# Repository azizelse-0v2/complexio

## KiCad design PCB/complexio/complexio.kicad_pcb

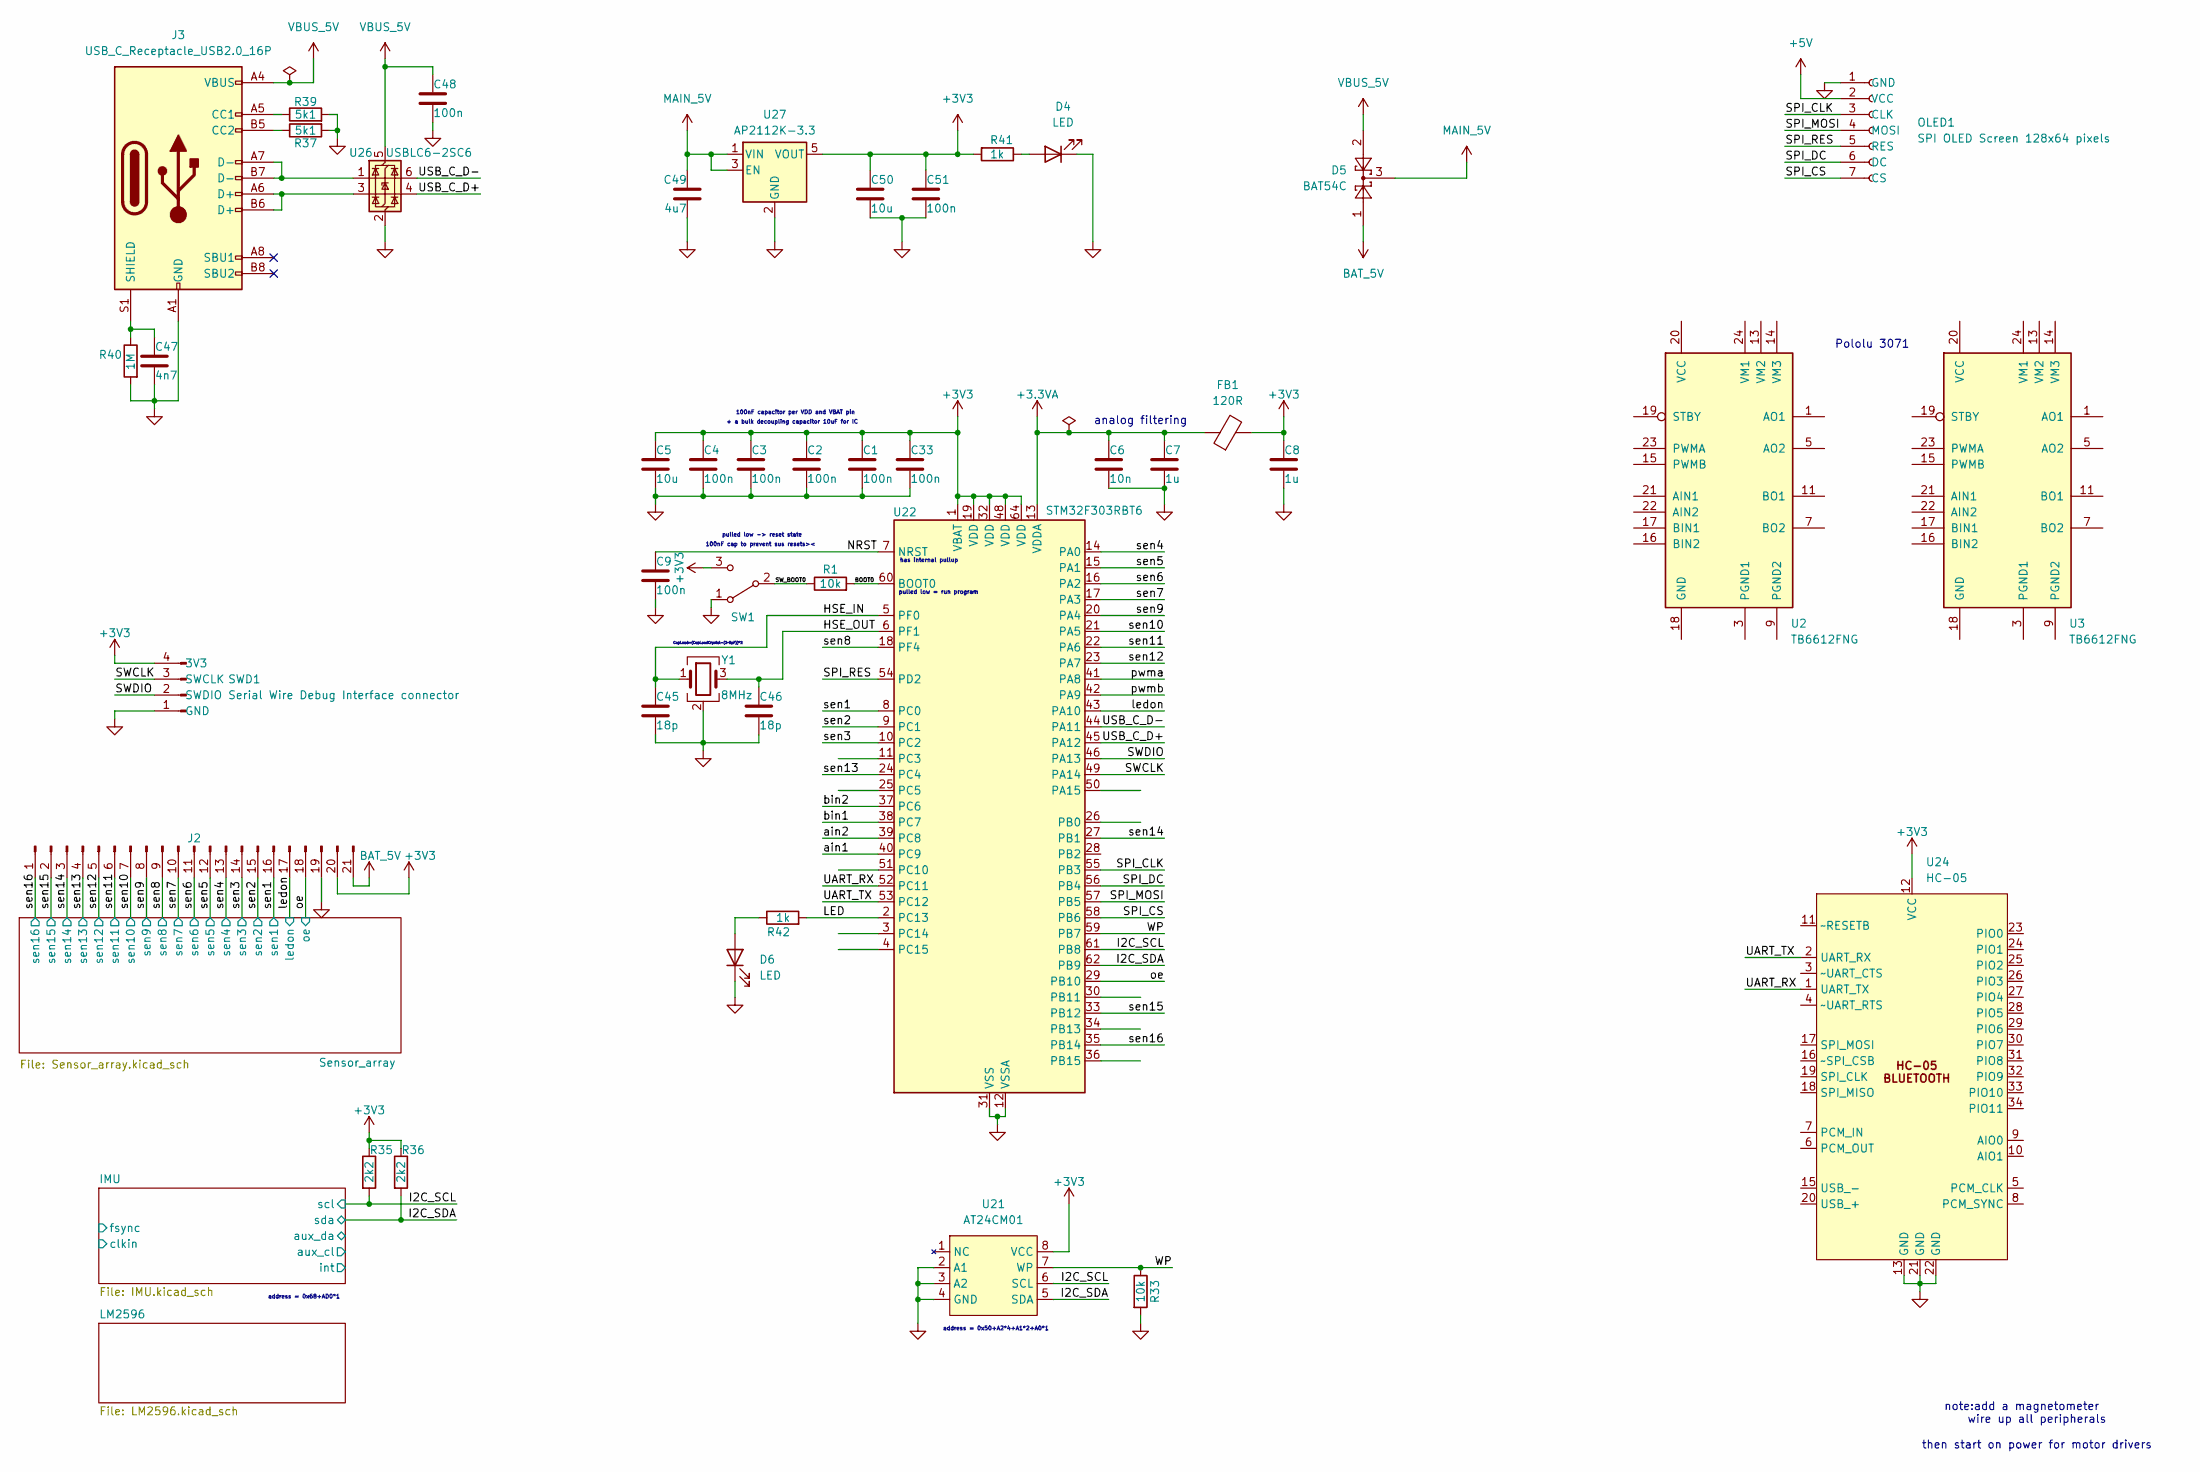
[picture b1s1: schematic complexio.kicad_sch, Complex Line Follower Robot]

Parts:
C1, C2, C3, C4, C9, C33, C48, C51: 100n; C_0402_1005Metric; MFR.Part # CL05B104KO5NNNC; JLCPCB Part # C1525
C5, C50: 10u; C_0603_1608Metric; MFR.Part # CL10A106MQ8NNNC; JLCPCB Part # C1691
C6: 10n; C_0402_1005Metric; MFR.Part # CL05B103KB5NNNC; JLCPCB Part # C15195
C7, C8: 1u; C_0402_1005Metric; MFR.Part # CL05A105KP5NNNC; JLCPCB Part # C14445
C45, C46: 18p; C_0402_1005Metric; MFR.Part # 0402CG180J500NT; JLCPCB Part # C1549
C47: 4n7; C_1206_3216Metric; MFR.Part # 1206B472K501NT; JLCPCB Part # C30323
C49: 4u7; C_0603_1608Metric; MFR.Part # CL10A475KP8NNNC; JLCPCB Part # C1705
D4, D6: LED; LED_0201_0603Metric; MFR.Part # KT-0603R; JLCPCB Part # C2286
D5: BAT54C; SOT-23; MFR.Part # MBR2060CT-LJ; JLCPCB Part # C82585
FB1: 120R; L_0603_1608Metric; MFR.Part # VHF160808H1N8ST; JLCPCB Part # C1026
J2: Conn_01x21_Pin; PinHeader_1x21_P1.27mm_Horizontal; MFR.Part # PZ1.27-1*50; JLCPCB Part # C5360892
J3: USB_C_Receptacle_USB2.0_16P; USB_C_Receptacle_GCT_USB4105-xx-A_16P_TopMnt_Horizontal
OLED1: SPI OLED Screen 128x64 pixels; SSD1306_SPI; MFR.Part # KH-2.54FH-1X7P-H8.5; JLCPCB Part # C2932672
R1, R33: 10k; R_0402_1005Metric; MFR.Part # RCT0210KJLF; JLCPCB Part # C174175
R35, R36: 2k2; R_0603_1608Metric; MFR.Part # 0603WAF2201T5E; JLCPCB Part # C4190
R37, R39: 5k1; R_0603_1608Metric; MFR.Part # 0603WAF5101T5E; JLCPCB Part # C23186
R40: 1M; R_1206_3216Metric; MFR.Part # HR1206J1M00P05Z; JLCPCB Part # C175518
R41, R42: 1k; R_1206_3216Metric; MFR.Part # 1206W4J0102T5E; JLCPCB Part # C1469
SW1: SW_SPDT; SW_E-Switch_EG1224_SPDT_Angled; MFR.Part # EG1224; JLCPCB Part # C273395
SWD1: Serial Wire Debug Interface connector; PinHeader_1x04_P2.54mm_Horizontal; MFR.Part # 2.54-1*4P反弯排针; JLCPCB Part # C91552
U2, U3: TB6612FNG; SSOP-24_5.3x8.2mm_P0.65mm; MFR.Part # TB6612FNG,C,8,EL; JLCPCB Part # C141517
U21: AT24CM01; MFR.Part # AT24CM01-SHD-T; JLCPCB Part # C36057
U22: STM32F303RBT6; LQFP-64_10x10mm_P0.5mm; MFR.Part # STM32F303RBT6; JLCPCB Part # C130453
U24: HC-05; HC-05_SMD
U26: USBLC6-2SC6; SOT-23-6
U27: AP2112K-3.3; SOT-23-5
Y1: 8MHz; Crystal_SMD_3225-4Pin_3.2x2.5mm; MFR.Part # XXDCELNANF-8MHZ

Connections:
+3.3VA: C6.1, C7.1, FB1.1, U22.13 (VDDA)
+3V3: C1.1, C2.1, C3.1, C4.1, C5.1, C8.1, C33.1, C50.1, C51.1, FB1.2, J2.20, R35.1, R36.1, R41.2, SW1.3 (C), SWD1.4 (3V3), U21.8 (VCC), U22.1 (VBAT), U22.19 (VDD), U22.32 (VDD), U22.48 (VDD), U22.64 (VDD), U24.12 (VCC), U27.5 (VOUT); also elsewhere on the board
+5V: OLED1.2 (VCC)
/BOOT0: R1.2, U22.60 (BOOT0)
/HSE_IN: C45.1, U22.5 (PF0), Y1.1
/HSE_OUT: C46.1, U22.6 (PF1), Y1.3
/I2C_SCL: R35.2, U21.6 (SCL), U22.61 (PB8); also elsewhere on the board
/I2C_SDA: R36.2, U21.5 (SDA), U22.62 (PB9); also elsewhere on the board
/LED: R42.2, U22.2 (PC13)
/NRST: C9.1, U22.7 (NRST)
/SPI_CLK: OLED1.3 (CLK), U22.55 (PB3)
/SPI_CS: OLED1.7 (CS), U22.58 (PB6)
/SPI_DC: OLED1.6 (DC), U22.56 (PB4)
/SPI_MOSI: OLED1.4 (MOSI), U22.57 (PB5)
/SPI_RES: OLED1.5 (RES), U22.54 (PD2)
/SWCLK: SWD1.3 (SWCLK), U22.49 (PA14)
/SWDIO: SWD1.2 (SWDIO), U22.46 (PA13)
/SW_BOOT0: R1.1, SW1.2 (B)
/UART_RX: U22.52 (PC11), U24.1 (UART_TX)
/UART_TX: U22.53 (PC12), U24.2 (UART_RX)
/USB_C_D+: U22.45 (PA12), U26.4 (I/O2)
/USB_C_D-: U22.44 (PA11), U26.6 (I/O1)
/WP: R33.1, U21.7 (WP), U22.59 (PB7)
/ain1: U22.40 (PC9)
/ain2: U22.39 (PC8)
/bin1: U22.38 (PC7)
/bin2: U22.37 (PC6)
/ledon: J2.17, U22.43 (PA10); also elsewhere on the board
/oe: J2.18, U22.29 (PB10); also elsewhere on the board
/pwma: U22.41 (PA8)
/pwmb: U22.42 (PA9)
/sen1: J2.16, U22.8 (PC0); also elsewhere on the board
/sen2: J2.15, U22.9 (PC1); also elsewhere on the board
/sen3: J2.14, U22.10 (PC2); also elsewhere on the board
/sen4: J2.13, U22.14 (PA0); also elsewhere on the board
/sen5: J2.12, U22.15 (PA1); also elsewhere on the board
/sen6: J2.11, U22.16 (PA2); also elsewhere on the board
/sen7: J2.10, U22.17 (PA3); also elsewhere on the board
/sen8: J2.9, U22.18 (PF4); also elsewhere on the board
/sen9: J2.8, U22.20 (PA4); also elsewhere on the board
/sen10: J2.7, U22.21 (PA5); also elsewhere on the board
/sen11: J2.6, U22.22 (PA6); also elsewhere on the board
/sen12: J2.5, U22.23 (PA7); also elsewhere on the board
/sen13: J2.4, U22.24 (PC4); also elsewhere on the board
/sen14: J2.3, U22.27 (PB1); also elsewhere on the board
/sen15: J2.2, U22.33 (PB12); also elsewhere on the board
/sen16: J2.1, U22.35 (PB14); also elsewhere on the board
BAT_5V: D5.1, J2.21; also elsewhere on the board
GND: C1.2, C2.2, C3.2, C4.2, C5.2, C6.2, C7.2, C8.2, C9.2, C33.2, C45.2, C46.2, C47.2, C48.2, C49.2, C50.2, C51.2, D4.1 (K), D6.1 (K), J2.19, J3.A1 (GND), J3.A12 (GND), J3.B1 (GND), J3.B12 (GND), OLED1.1 (GND), R33.2, R37.2, R39.2, R40.2, SW1.1 (A), SWD1.1 (GND), U21.2 (A1), U21.3 (A2), U21.4 (GND), U22.12 (VSSA), U22.31 (VSS), U22.47 (VSS), U22.63 (VSS), U24.13 (GND), U24.21 (GND), U24.22 (GND), U26.2 (GND), U27.2 (GND), Y1.2 (G), Y1.4 (G); also elsewhere on the board
MAIN_5V: C49.1, D5.3, U27.1 (VIN), U27.3 (EN); also elsewhere on the board
unnamed: D4.2 (A), R41.1
unnamed: D6.2 (A), R42.1
unnamed: J3.A5 (CC1), R39.1
unnamed: J3.B5 (CC2), R37.1
unnamed: J3.A6 (D+), J3.B6 (D+), U26.3 (I/O2)
unnamed: J3.A7 (D-), J3.B7 (D-), U26.1 (I/O1)
unnamed: C47.1, J3.S1 (SHIELD), R40.1
unnamed: U2.1 (AO1), U2.2 (AO1)
unnamed: U2.5 (AO2), U2.6 (AO2)
unnamed: U2.11 (BO1), U2.12 (BO1)
unnamed: U2.7 (BO2), U2.8 (BO2)
unnamed: U2.3 (PGND1), U2.4 (PGND1)
unnamed: U2.9 (PGND2), U2.10 (PGND2)
unnamed: U3.1 (AO1), U3.2 (AO1)
unnamed: U3.5 (AO2), U3.6 (AO2)
unnamed: U3.11 (BO1), U3.12 (BO1)
unnamed: U3.7 (BO2), U3.8 (BO2)
unnamed: U3.3 (PGND1), U3.4 (PGND1)
unnamed: U3.9 (PGND2), U3.10 (PGND2)
VBUS_5V: C48.1, D5.2, J3.A4 (VBUS), J3.A9 (VBUS), J3.B4 (VBUS), J3.B9 (VBUS), U26.5 (VBUS)

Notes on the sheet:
+ a bulk decoupling capacitor 10uF for IC
pulled low -> reset state
100nF capacitor per VDD and VBAT pin
has internal pullup
note:add a magnetometer wire up all peripherals then start on power for motor drivers
address = 0x68+AD0*1
analog filtering
100nF cap to prevent sus resets><
pulled low = run program
Pololu 3071
address = 0x50+A2*4+A1*2+A0*1
CapLoad=(CapLoadCrystal-(3~5pF))*2

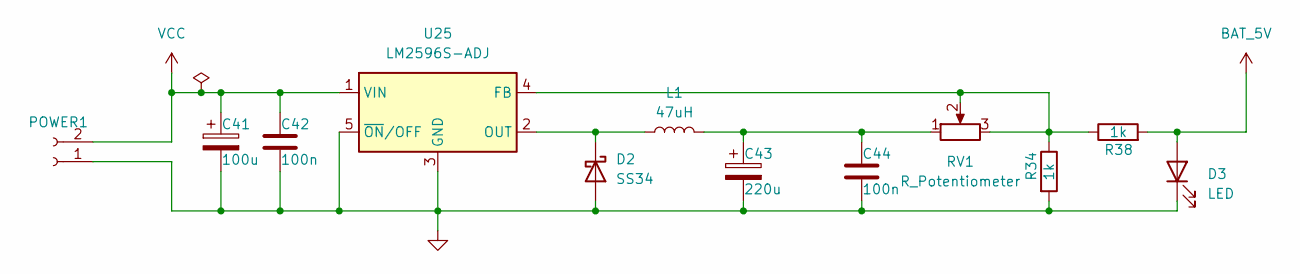
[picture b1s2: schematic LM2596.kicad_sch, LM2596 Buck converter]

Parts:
C41: 100u; CP_Elec_8x10
C42, C44: 100n; C_0402_1005Metric; MFR.Part # CL05B104KO5NNNC; JLCPCB Part # C1525
C43: 220u; CP_Elec_8x10
D2: SS34; D_SMA; MFR.Part # B340LA-13-F; JLCPCB Part # C17101
D3: LED; LED_0201_0603Metric; MFR.Part # KT-0603R; JLCPCB Part # C2286
L1: 47uH; L_Bourns_SRR1208_12.7x12.7mm
POWER1: Conn_01x02_Socket; AMASS_XT60-M_1x02_P7.20mm_Vertical; MFR.Part # XT60-M.; JLCPCB Part # C98733
R34, R38: 1k; R_1206_3216Metric; MFR.Part # 1206W4J0102T5E; JLCPCB Part # C1469
RV1: R_Potentiometer; Potentiometer_Bourns_3296W_Vertical
U25: LM2596S-ADJ; TO-263-5_TabPin3; MFR.Part # LM2596R-ADJ; JLCPCB Part # C52684

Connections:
BAT_5V: D3.2 (A), R38.2; also elsewhere on the board
GND: C41.2, C42.2, C43.2, C44.2, D2.2 (A), D3.1 (K), POWER1.1, R34.2, U25.3 (GND), U25.5 (~ON/OFF); also elsewhere on the board
unnamed: C43.1, C44.1, L1.2, RV1.1
unnamed: D2.1 (K), L1.1, U25.2 (OUT)
unnamed: R34.1, R38.1, RV1.2, RV1.3, U25.4 (FB)
VCC: C41.1, C42.1, POWER1.2, U25.1 (VIN)

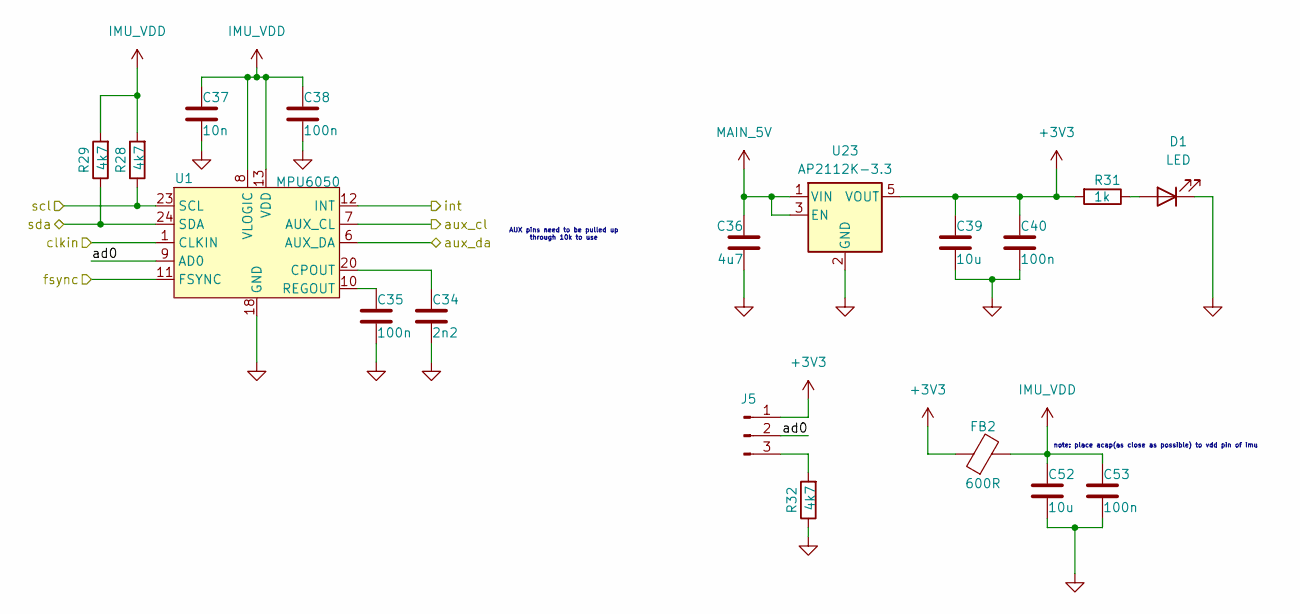
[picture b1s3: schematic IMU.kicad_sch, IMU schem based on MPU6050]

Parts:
C34: 2n2; C_0402_1005Metric; MFR.Part # CC0402KRX7R9BB222; JLCPCB Part # C106861
C35, C38, C40, C53: 100n; C_0402_1005Metric; MFR.Part # CL05B104KO5NNNC; JLCPCB Part # C1525
C36: 4u7; C_0603_1608Metric; MFR.Part # CL10A475KP8NNNC; JLCPCB Part # C1705
C37: 10n; C_0402_1005Metric; MFR.Part # CL05B103KB5NNNC; JLCPCB Part # C15195
C39, C52: 10u; C_0603_1608Metric; MFR.Part # CL10A106MQ8NNNC; JLCPCB Part # C1691
D1: LED; LED_0201_0603Metric; MFR.Part # KT-0603R; JLCPCB Part # C2286
FB2: 600R; L_0603_1608Metric; MFR.Part # BLM18AG601SN1D; JLCPCB Part # C19330
J5: Conn_01x03_Pin; PinSocket_1x03_P2.54mm_Vertical; MFR.Part # 2.54-1*3PPin; JLCPCB Part # C49257
R28, R29, R32: 4k7; R_0402_1005Metric; MFR.Part # 0402WGF4701TCE; JLCPCB Part # C25900
R31: 1k; R_1206_3216Metric; MFR.Part # 1206W4J0102T5E; JLCPCB Part # C1469
U1: MPU6050; MPU6050SMD
U23: AP2112K-3.3; SOT-23-5

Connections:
+3V3: C39.1, C40.1, FB2.1, J5.1, R31.2, U23.5 (VOUT); also elsewhere on the board
/I2C_SCL: R28.1, U1.23 (SCL); also elsewhere on the board
/I2C_SDA: R29.1, U1.24 (SDA); also elsewhere on the board
/IMU/ad0: J5.2, U1.9 (AD0)
/IMU/aux_cl: U1.7 (AUX_CL)
/IMU/aux_da: U1.6 (AUX_DA)
/IMU/clkin: U1.1 (CLKIN)
/IMU/fsync: U1.11 (FSYNC)
/IMU/int: U1.12 (INT)
GND: C34.2, C35.2, C36.2, C37.2, C38.2, C39.2, C40.2, C52.2, C53.2, D1.1 (K), R32.1, U1.18 (GND), U23.2 (GND); also elsewhere on the board
IMU_VDD: C37.1, C38.1, C52.1, C53.1, FB2.2, R28.2, R29.2, U1.8 (VLOGIC), U1.13 (VDD)
MAIN_5V: C36.1, U23.1 (VIN), U23.3 (EN); also elsewhere on the board
unnamed: D1.2 (A), R31.1
unnamed: J5.3, R32.2
unnamed: C34.1, U1.20 (CPOUT)
unnamed: C35.1, U1.10 (REGOUT)

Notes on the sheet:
AUX pins need to be pulled up through 10k to use
note: place acap(as close as possible) to vdd pin of imu

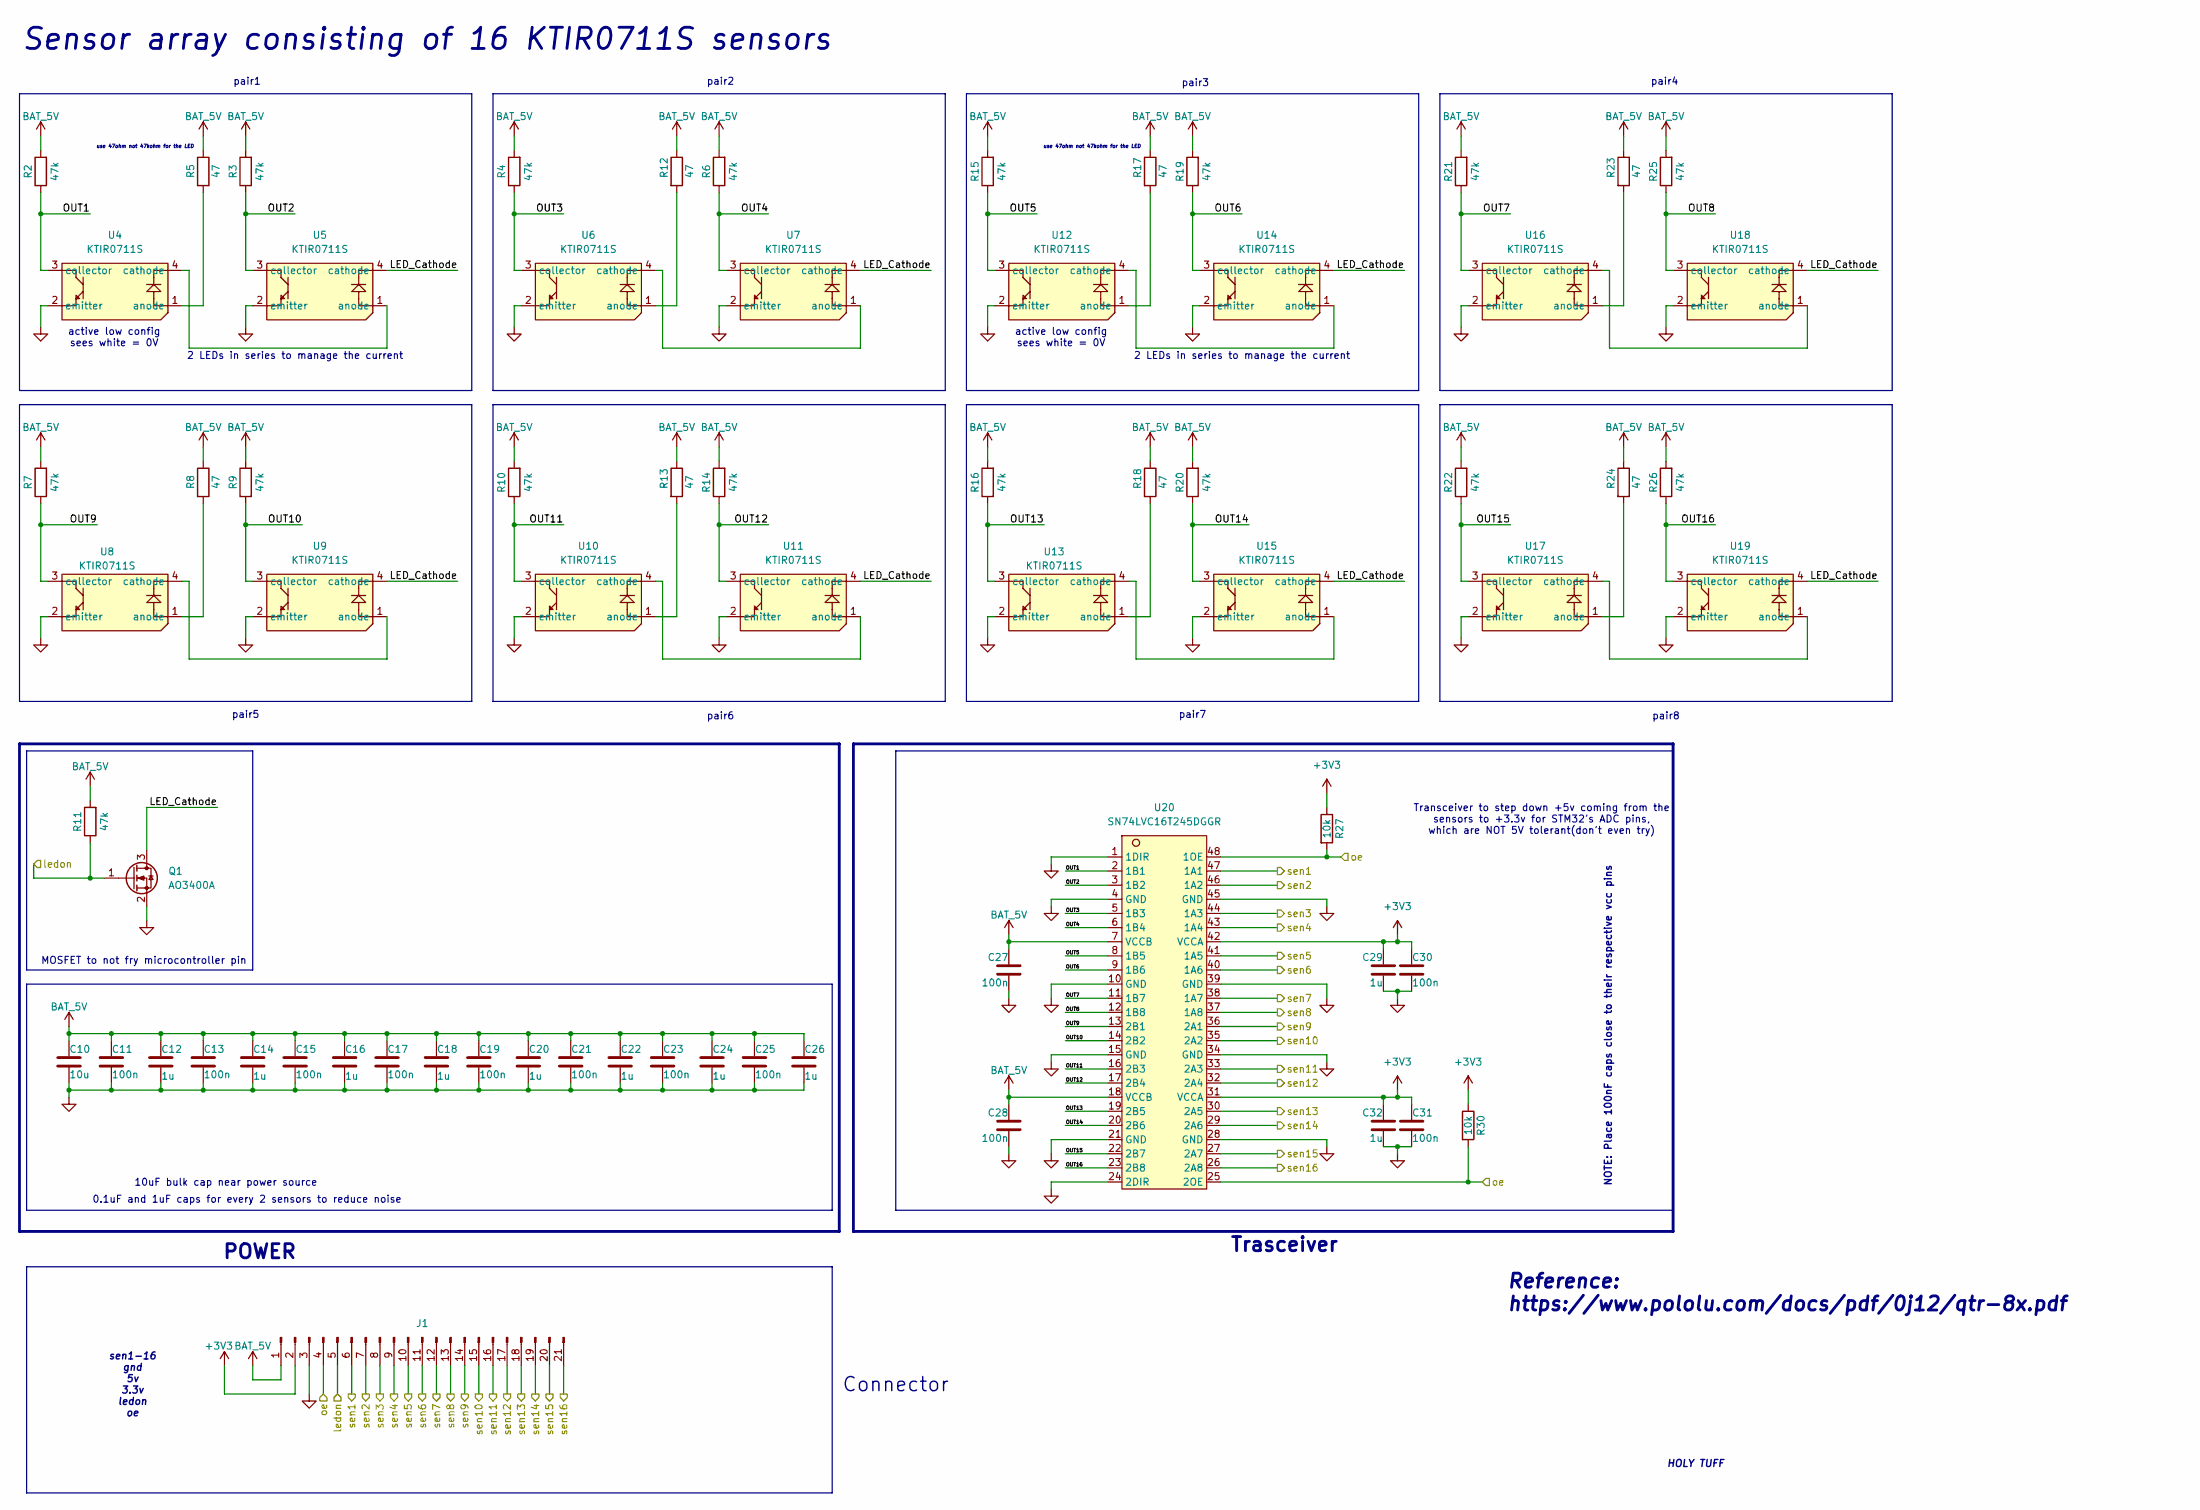
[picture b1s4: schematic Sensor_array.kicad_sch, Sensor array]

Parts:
C10: 10u; C_0603_1608Metric; MFR.Part # CL10A106MQ8NNNC; JLCPCB Part # C1691
C11, C13, C15, C17, C19, C21, C23, C25, C27, C28, C30, C31: 100n; C_0402_1005Metric; MFR.Part # CL05B104KO5NNNC; JLCPCB Part # C1525
C12, C14, C16, C18, C20, C22, C24, C26, C29, C32: 1u; C_0402_1005Metric; MFR.Part # CL05A105KP5NNNC; JLCPCB Part # C14445
J1: Conn_01x21_Pin; PinHeader_1x21_P1.27mm_Horizontal; MFR.Part # PZ1.27-1*50; JLCPCB Part # C5360892
Q1: AO3400A; SOT-23
R2, R3, R4, R6, R7, R9, R10, R11, R14, R15, R16, R19, R20, R21, R22, R25, R26: 47k; R_0402_1005Metric; MFR.Part # RCA0247KJLF; JLCPCB Part # C22356233
R5, R8, R12, R13, R17, R18, R23, R24: 47; R_1206_3216Metric; MFR.Part # RCT0647RJLF; JLCPCB Part # C702856
R27, R30: 10k; R_0402_1005Metric; MFR.Part # RCT0210KJLF; JLCPCB Part # C174175
U4, U5, U6, U7, U8, U9, U10, U11, U12, U13, U14, U15, U16, U17, U18, U19: KTIR0711S; MFR.Part # KTIR0711S; JLCPCB Part # C3034700
U20: SN74LVC16T245DGGR

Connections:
+3V3: C29.1, C30.1, C31.1, C32.1, J1.2, R27.1, R30.1, U20.31 (VCCA), U20.42 (VCCA); also elsewhere on the board
/Sensor_array/LED_Cathode: Q1.3 (D), U5.4 (cathode), U7.4 (cathode), U9.4 (cathode), U11.4 (cathode), U14.4 (cathode), U15.4 (cathode), U18.4 (cathode), U19.4 (cathode)
/Sensor_array/OUT1: R2.1, U4.3 (collector), U20.2 (1B1)
/Sensor_array/OUT2: R3.1, U5.3 (collector), U20.3 (1B2)
/Sensor_array/OUT3: R4.1, U6.3 (collector), U20.5 (1B3)
/Sensor_array/OUT4: R6.1, U7.3 (collector), U20.6 (1B4)
/Sensor_array/OUT5: R15.1, U12.3 (collector), U20.8 (1B5)
/Sensor_array/OUT6: R19.1, U14.3 (collector), U20.9 (1B6)
/Sensor_array/OUT7: R21.1, U16.3 (collector), U20.11 (1B7)
/Sensor_array/OUT8: R25.1, U18.3 (collector), U20.12 (1B8)
/Sensor_array/OUT9: R7.1, U8.3 (collector), U20.13 (2B1)
/Sensor_array/OUT10: R9.1, U9.3 (collector), U20.14 (2B2)
/Sensor_array/OUT11: R10.1, U10.3 (collector), U20.16 (2B3)
/Sensor_array/OUT12: R14.1, U11.3 (collector), U20.17 (2B4)
/Sensor_array/OUT13: R16.1, U13.3 (collector), U20.19 (2B5)
/Sensor_array/OUT14: R20.1, U15.3 (collector), U20.20 (2B6)
/Sensor_array/OUT15: R22.1, U17.3 (collector), U20.22 (2B7)
/Sensor_array/OUT16: R26.1, U19.3 (collector), U20.23 (2B8)
/ledon: J1.5, Q1.1 (G), R11.1; also elsewhere on the board
/oe: J1.4, R27.2, R30.2, U20.25 (2OE), U20.48 (1OE); also elsewhere on the board
/sen1: J1.6, U20.47 (1A1); also elsewhere on the board
/sen2: J1.7, U20.46 (1A2); also elsewhere on the board
/sen3: J1.8, U20.44 (1A3); also elsewhere on the board
/sen4: J1.9, U20.43 (1A4); also elsewhere on the board
/sen5: J1.10, U20.41 (1A5); also elsewhere on the board
/sen6: J1.11, U20.40 (1A6); also elsewhere on the board
/sen7: J1.12, U20.38 (1A7); also elsewhere on the board
/sen8: J1.13, U20.37 (1A8); also elsewhere on the board
/sen9: J1.14, U20.36 (2A1); also elsewhere on the board
/sen10: J1.15, U20.35 (2A2); also elsewhere on the board
/sen11: J1.16, U20.33 (2A3); also elsewhere on the board
/sen12: J1.17, U20.32 (2A4); also elsewhere on the board
/sen13: J1.18, U20.30 (2A5); also elsewhere on the board
/sen14: J1.19, U20.29 (2A6); also elsewhere on the board
/sen15: J1.20, U20.27 (2A7); also elsewhere on the board
/sen16: J1.21, U20.26 (2A8); also elsewhere on the board
BAT_5V: C10.1, C11.1, C12.1, C13.1, C14.1, C15.1, C16.1, C17.1, C18.1, C19.1, C20.1, C21.1, C22.1, C23.1, C24.1, C25.1, C26.1, C27.1, C28.1, J1.1, R2.2, R3.2, R4.2, R5.1, R6.2, R7.2, R8.1, R9.2, R10.2, R11.2, R12.1, R13.1, R14.2, R15.2, R16.2, R17.1, R18.1, R19.2, R20.2, R21.2, R22.2, R23.1, R24.1, R25.2, R26.2, U20.7 (VCCB), U20.18 (VCCB); also elsewhere on the board
GND: C10.2, C11.2, C12.2, C13.2, C14.2, C15.2, C16.2, C17.2, C18.2, C19.2, C20.2, C21.2, C22.2, C23.2, C24.2, C25.2, C26.2, C27.2, C28.2, C29.2, C30.2, C31.2, C32.2, J1.3, Q1.2 (S), U4.2 (emitter), U5.2 (emitter), U6.2 (emitter), U7.2 (emitter), U8.2 (emitter), U9.2 (emitter), U10.2 (emitter), U11.2 (emitter), U12.2 (emitter), U13.2 (emitter), U14.2 (emitter), U15.2 (emitter), U16.2 (emitter), U17.2 (emitter), U18.2 (emitter), U19.2 (emitter), U20.1 (1DIR), U20.4 (GND), U20.10 (GND), U20.15 (GND), U20.21 (GND), U20.24 (2DIR), U20.28 (GND), U20.34 (GND), U20.39 (GND), U20.45 (GND); also elsewhere on the board
unnamed: R5.2, U4.1 (anode)
unnamed: U4.4 (cathode), U5.1 (anode)
unnamed: R12.2, U6.1 (anode)
unnamed: U6.4 (cathode), U7.1 (anode)
unnamed: R8.2, U8.1 (anode)
unnamed: U8.4 (cathode), U9.1 (anode)
unnamed: R13.2, U10.1 (anode)
unnamed: U10.4 (cathode), U11.1 (anode)
unnamed: R17.2, U12.1 (anode)
unnamed: U12.4 (cathode), U14.1 (anode)
unnamed: R18.2, U13.1 (anode)
unnamed: U13.4 (cathode), U15.1 (anode)
unnamed: R23.2, U16.1 (anode)
unnamed: U16.4 (cathode), U18.1 (anode)
unnamed: R24.2, U17.1 (anode)
unnamed: U17.4 (cathode), U19.1 (anode)

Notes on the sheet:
2 LEDs in series to manage the current
Reference: https://www.pololu.com/docs/pdf/0j12/qtr-8x.pdf
pair8
sen1-16 gnd 5v 3.3v ledon oe
0.1uF and 1uF caps for every 2 sensors to reduce noise
Trasceiver
pair2
pair5
pair3
NOTE: Place 100nF caps close to their respective vcc pins
Sensor array consisting of 16 KTIR0711S sensors
HOLY TUFF
pair4
pair1
MOSFET to not fry microcontroller pin
pair7
POWER
Connector
pair6
active low config sees white = 0V
10uF bulk cap near power source
use 47ohm not 47kohm for the LED
Transceiver to step down +5v coming from the sensors to +3.3v for STM32's ADC pins, which are NOT 5V tolerant(don't even try)

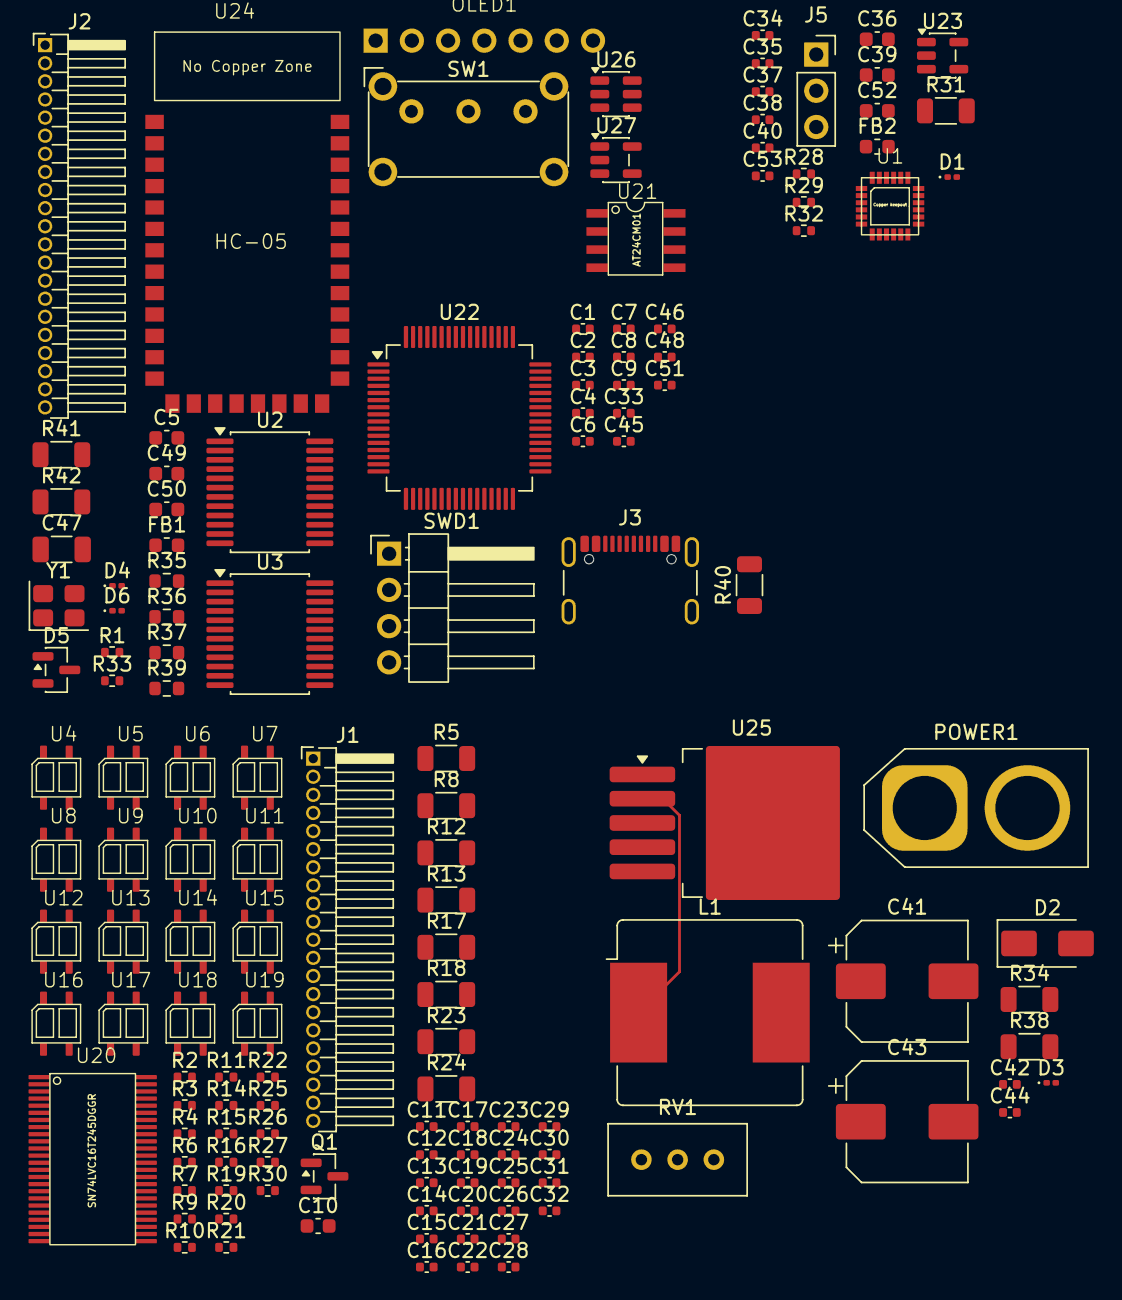
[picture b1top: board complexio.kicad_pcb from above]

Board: 2 copper layers, 142 parts (0 on the bottom side), 106 nets.

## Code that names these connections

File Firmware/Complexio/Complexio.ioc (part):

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Mcu.Name=STM32F303R(B-C)Tx
Mcu.Package=LQFP64
Mcu.UserName=STM32F303RBTx
PA0.GPIOParameters=GPIO_Label
PA0.GPIO_Label=sen4
PA0.Mode=IN1-Single-Ended
PA0.Signal=ADC1_IN1
PA1.GPIOParameters=GPIO_Label
PA1.GPIO_Label=sen5
PA1.Mode=IN2-Single-Ended
PA1.Signal=ADC1_IN2
PA11.Mode=Device
PA11.Signal=USB_DM
PA12.Mode=Device
PA12.Signal=USB_DP
PA13.Mode=Serial_Wire
PA13.Signal=SYS_JTMS-SWDIO
PA14.Mode=Serial_Wire
PA14.Signal=SYS_JTCK-SWCLK
PA2.GPIOParameters=GPIO_Label
PA2.GPIO_Label=sen6
PA2.Mode=IN3-Single-Ended
PA2.Signal=ADC1_IN3
PA3.GPIOParameters=GPIO_Label
PA3.GPIO_Label=sen7
PA3.Mode=IN4-Single-Ended
PA3.Signal=ADC1_IN4
PA4.GPIOParameters=GPIO_Label
PA4.GPIO_Label=sen9
PA4.Mode=IN1-Single-Ended
PA4.Signal=ADC2_IN1
PA5.GPIOParameters=GPIO_Label
PA5.GPIO_Label=sen10
PA5.Mode=IN2-Single-Ended
PA5.Signal=ADC2_IN2
PA6.GPIOParameters=GPIO_Label
PA6.GPIO_Label=sen11
PA6.Mode=IN3-Single-Ended
PA6.Signal=ADC2_IN3
PA7.GPIOParameters=GPIO_Label
PA7.GPIO_Label=sen12
PA7.Mode=IN4-Single-Ended
PA7.Signal=ADC2_IN4
PA8.GPIOParameters=GPIO_Label
PA8.GPIO_Label=pwma
PA8.Signal=S_TIM1_CH1
PA9.GPIOParameters=GPIO_Label
PA9.GPIO_Label=pwmb
PA9.Signal=S_TIM1_CH2
PB1.GPIOParameters=GPIO_Label
PB1.GPIO_Label=sen14
PB1.Mode=IN1-Single-Ended
PB1.Signal=ADC3_IN1
PB12.GPIOParameters=GPIO_Label
PB12.GPIO_Label=sen15
PB12.Mode=IN3-Single-Ended
PB12.Signal=ADC4_IN3
PB14.GPIOParameters=GPIO_Label
PB14.GPIO_Label=sen16
PB14.Mode=IN4-Single-Ended
PB14.Signal=ADC4_IN4
PB3.Mode=Simplex_Bidirectional_Master
PB3.Signal=SPI1_SCK
PB4.GPIOParameters=GPIO_Label
PB4.GPIO_Label=DC
PB4.Signal=GPIO_Output
PB5.Mode=Simplex_Bidirectional_Master
PB5.Signal=SPI1_MOSI
PB6.GPIOParameters=GPIO_Label
PB6.GPIO_Label=CS
PB6.Signal=GPIO_Output
PB8.Mode=I2C
PB8.Signal=I2C1_SCL
PB9.Mode=I2C
PB9.Signal=I2C1_SDA
PC0.GPIOParameters=GPIO_Label
PC0.GPIO_Label=sen1
PC0.Signal=ADCx_IN6
PC1.GPIOParameters=GPIO_Label
PC1.GPIO_Label=sen2
PC1.Signal=ADCx_IN7
PC10.GPIOParameters=GPIO_Label
PC10.GPIO_Label=tx
PC10.Mode=Asynchronous
PC10.Signal=UART4_TX
PC11.GPIOParameters=GPIO_Label
PC11.GPIO_Label=rx
PC11.Mode=Asynchronous
PC11.Signal=UART4_RX
PC13.GPIOParameters=GPIO_Label
PC13.GPIO_Label=LED
PC13.Signal=GPIO_Output
PC2.GPIOParameters=GPIO_Label
PC2.GPIO_Label=sen3
PC2.Signal=ADCx_IN8
PC4.GPIOParameters=GPIO_Label
PC4.GPIO_Label=sen13
PC4.Mode=IN5-Single-Ended
PC4.Signal=ADC2_IN5
PC6.GPIOParameters=GPIO_Label
PC6.GPIO_Label=bin2
PC6.Signal=GPIO_Output
PC7.GPIOParameters=GPIO_Label
PC7.GPIO_Label=bin1
PC7.Signal=GPIO_Output
PC8.GPIOParameters=GPIO_Label
PC8.GPIO_Label=ain2
PC8.Signal=GPIO_Output
PC9.GPIOParameters=GPIO_Label
PC9.GPIO_Label=ain1
PC9.Signal=GPIO_Output
PD2.GPIOParameters=GPIO_Label
PD2.GPIO_Label=RES
PD2.Signal=GPIO_Output
PF0-OSC_IN.Mode=HSE-External-Oscillator
PF0-OSC_IN.Signal=RCC_OSC_IN
PF1-OSC_OUT.Mode=HSE-External-Oscillator
PF1-OSC_OUT.Signal=RCC_OSC_OUT
PF4.GPIOParameters=GPIO_Label
PF4.GPIO_Label=sen8
PF4.Mode=IN5-Single-Ended
PF4.Signal=ADC1_IN5
RCC.HSEPLLFreq_Value=8000000
RCC.HSE_VALUE=8000000
RCC.SYSCLKFreq_VALUE=72000000
RCC.SYSCLKSourceVirtual=RCC_SYSCLKSOURCE_PLLCLK
board=custom

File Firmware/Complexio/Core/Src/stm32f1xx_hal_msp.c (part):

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    __HAL_RCC_GPIOA_CLK_ENABLE();
    __HAL_RCC_GPIOB_CLK_ENABLE();
    /**ADC1 GPIO Configuration
    PA0-WKUP     ------> ADC1_IN0
    PA1     ------> ADC1_IN1
    PA2     ------> ADC1_IN2
    PA3     ------> ADC1_IN3
    PB1     ------> ADC1_IN9
    */
    GPIO_InitStruct.Pin = GPIO_PIN_0|GPIO_PIN_1|GPIO_PIN_2|GPIO_PIN_3;
    GPIO_InitStruct.Mode = GPIO_MODE_ANALOG;
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
    __HAL_RCC_GPIOA_CLK_ENABLE();
    /**ADC2 GPIO Configuration
    PA0-WKUP     ------> ADC2_IN0
    PA1     ------> ADC2_IN1
    PA2     ------> ADC2_IN2
    PA3     ------> ADC2_IN3
    */
    GPIO_InitStruct.Pin = GPIO_PIN_0|GPIO_PIN_1|GPIO_PIN_2|GPIO_PIN_3;
    GPIO_InitStruct.Mode = GPIO_MODE_ANALOG;
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    __HAL_RCC_ADC1_CLK_DISABLE();

    /**ADC1 GPIO Configuration
    PA0-WKUP     ------> ADC1_IN0
    PA1     ------> ADC1_IN1
    PA2     ------> ADC1_IN2
    PA3     ------> ADC1_IN3
    PB1     ------> ADC1_IN9
    */
    HAL_GPIO_DeInit(GPIOA, GPIO_PIN_0|GPIO_PIN_1|GPIO_PIN_2|GPIO_PIN_3);

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    __HAL_RCC_ADC2_CLK_DISABLE();

    /**ADC2 GPIO Configuration
    PA0-WKUP     ------> ADC2_IN0
    PA1     ------> ADC2_IN1
    PA2     ------> ADC2_IN2
    PA3     ------> ADC2_IN3
    */
    HAL_GPIO_DeInit(GPIOA, GPIO_PIN_0|GPIO_PIN_1|GPIO_PIN_2|GPIO_PIN_3);

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
    __HAL_RCC_GPIOA_CLK_ENABLE();
    /**SPI1 GPIO Configuration
    PA5     ------> SPI1_SCK
    PA7     ------> SPI1_MOSI
    */
    GPIO_InitStruct.Pin = GPIO_PIN_5|GPIO_PIN_7;
    GPIO_InitStruct.Mode = GPIO_MODE_AF_PP;
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    __HAL_RCC_SPI1_CLK_DISABLE();

    /**SPI1 GPIO Configuration
    PA5     ------> SPI1_SCK
    PA7     ------> SPI1_MOSI
    */
    HAL_GPIO_DeInit(GPIOA, GPIO_PIN_5|GPIO_PIN_7);

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    __HAL_RCC_GPIOB_CLK_ENABLE();
    __HAL_RCC_GPIOA_CLK_ENABLE();
    /**TIM2 GPIO Configuration
    PB10     ------> TIM2_CH3
    PA15     ------> TIM2_CH1
    PB3     ------> TIM2_CH2
    */
    GPIO_InitStruct.Pin = GPIO_PIN_10|GPIO_PIN_3;
    GPIO_InitStruct.Mode = GPIO_MODE_AF_PP;
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    __HAL_RCC_GPIOA_CLK_ENABLE();
    /**USART1 GPIO Configuration
    PA9     ------> USART1_TX
    PA10     ------> USART1_RX
    */
    GPIO_InitStruct.Pin = GPIO_PIN_9;
    GPIO_InitStruct.Mode = GPIO_MODE_AF_PP;
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
    /**USART1 GPIO Configuration
    PA9     ------> USART1_TX
    PA10     ------> USART1_RX
    */
    HAL_GPIO_DeInit(GPIOA, GPIO_PIN_9|GPIO_PIN_10);

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
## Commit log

2026-03-21 Initial schem
2026-03-22 Initial code,schem & added assets
2026-03-22 Generated code using STM32CubeMX
2026-03-23 Sensor array finished & main schem modified
2026-03-24 Changed firmware & SMD of mpu6050+minor changes
2026-03-25 Advanced with schem & resolved main power problem

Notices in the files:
Firmware/Complexio/Core/Src/stm32f1xx_hal_msp.c:
Copyright (c) 2026 STMicroelectronics.
All rights reserved.
This software is licensed under terms that can be found in the LICENSE file
